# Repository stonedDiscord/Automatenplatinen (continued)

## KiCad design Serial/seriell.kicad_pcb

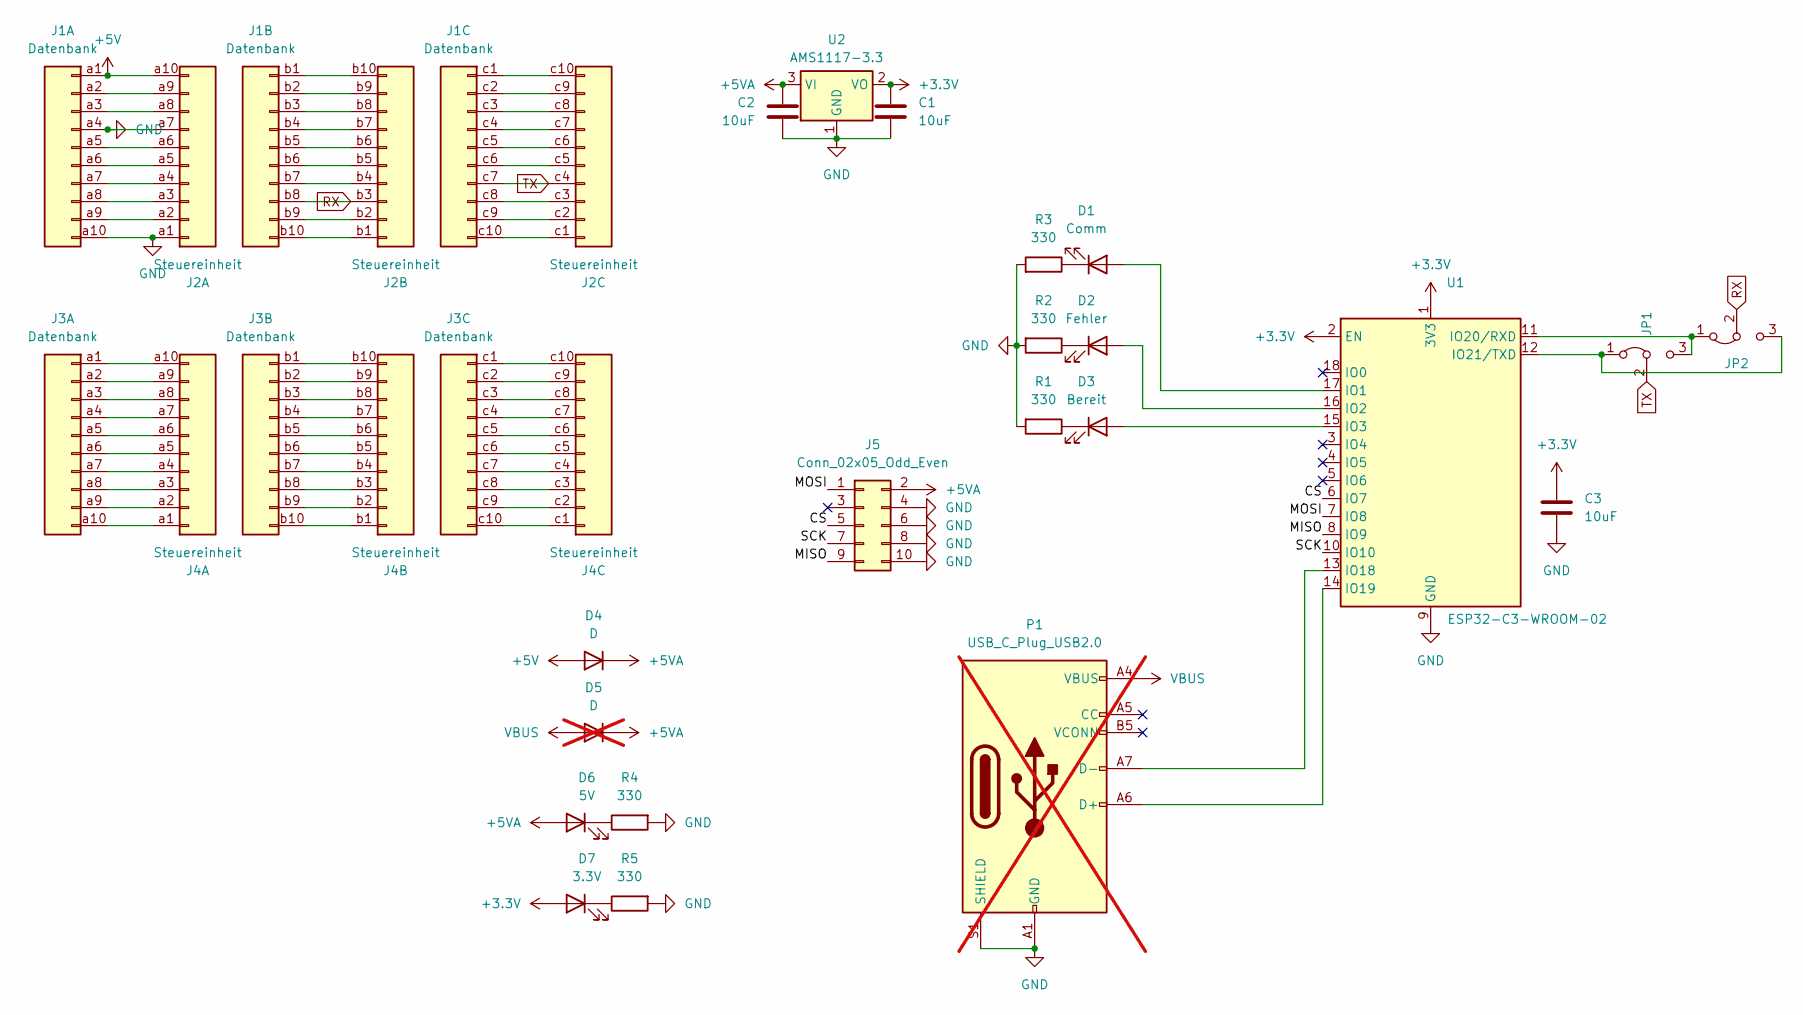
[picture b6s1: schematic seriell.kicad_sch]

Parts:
C1, C2, C3: 10uF; C_0603_1608Metric
D1: Comm; LED_0603_1608Metric
D2: Fehler; LED_0603_1608Metric
D3: Bereit; LED_0603_1608Metric
D4: D; D_SOD-123
D5: D; D_SOD-123; not fitted
D6: 5V; LED_0603_1608Metric
D7: 3.3V; LED_0603_1608Metric
J1, J3: Datenbank; DIN41612_C3_3x10_Female_Vertical_THT
J2, J4: Steuereinheit; DIN41612_R3_3x10_Male_Vertical_THT
J5: Conn_02x05_Odd_Even; IDC-Header_2x05_P2.54mm_Vertical
JP1: TX; SolderJumper-3_P1.3mm_Bridged2Bar12_Pad1.0x1.5mm
JP2: RX; SolderJumper-3_P1.3mm_Bridged2Bar12_Pad1.0x1.5mm
P1: USB_C_Plug_USB2.0; USB_C_Receptacle_G-Switch_GT-USB-7010ASV; not fitted
R1, R2, R3, R4, R5: 330; LED_0603_1608Metric
U1: ESP32-C3-WROOM-02
U2: AMS1117-3.3; SOT-223-3_TabPin2

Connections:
+3.3V: C1.1, C3.1, D7.2 (A), U1.1 (3V3), U1.2 (EN), U2.2 (VO)
+5V: D4.2 (A), J1.a1, J2.a10
+5VA: C2.1, D4.1 (K), D5.1 (K), D6.2 (A), J5.2, U2.3 (VI)
/CS: J5.5, U1.6 (IO7)
/MISO: J5.9, U1.8 (IO9)
/MOSI: J5.1, U1.7 (IO8)
/SCK: J5.7, U1.10 (IO10)
GND: C1.2, C2.2, C3.2, J1.a4, J1.a10, J2.a1, J2.a7, J5.4, J5.6, J5.8, J5.10, P1.A1 (GND), P1.A12 (GND), P1.B1 (GND), P1.B12 (GND), P1.S1 (SHIELD), R1.2, R2.2, R3.2, R4.2, R5.2, U1.9 (GND), U1.19 (GND), U2.1 (GND)
unnamed: D1.2 (A), U1.17 (IO1)
unnamed: D1.1 (K), R3.1
unnamed: D2.2 (A), U1.16 (IO2)
unnamed: D2.1 (K), R2.1
unnamed: D3.2 (A), U1.15 (IO3)
unnamed: D3.1 (K), R1.1
unnamed: D6.1 (K), R4.1
unnamed: D7.1 (K), R5.1
unnamed: J1.a2, J2.a9
unnamed: J1.a3, J2.a8
unnamed: J1.a5, J2.a6
unnamed: J1.a6, J2.a5
unnamed: J1.a7, J2.a4
unnamed: J1.a8, J2.a3
unnamed: J1.a9, J2.a2
unnamed: J1.b1, J2.b10
unnamed: J1.b2, J2.b9
unnamed: J1.b3, J2.b8
unnamed: J1.b4, J2.b7
unnamed: J1.b5, J2.b6
unnamed: J1.b6, J2.b5
unnamed: J1.b7, J2.b4
unnamed: J1.b9, J2.b2
unnamed: J1.b10, J2.b1
unnamed: J1.c1, J2.c10
unnamed: J1.c2, J2.c9
unnamed: J1.c3, J2.c8
unnamed: J1.c4, J2.c7
unnamed: J1.c5, J2.c6
unnamed: J1.c6, J2.c5
unnamed: J1.c8, J2.c3
unnamed: J1.c9, J2.c2
unnamed: J1.c10, J2.c1
unnamed: J3.a1, J4.a10
unnamed: J3.a2, J4.a9
unnamed: J3.a3, J4.a8
unnamed: J3.a4, J4.a7
unnamed: J3.a5, J4.a6
unnamed: J3.a6, J4.a5
unnamed: J3.a7, J4.a4
unnamed: J3.a8, J4.a3
unnamed: J3.a9, J4.a2
unnamed: J3.a10, J4.a1
unnamed: J3.b1, J4.b10
unnamed: J3.b2, J4.b9
unnamed: J3.b3, J4.b8
unnamed: J3.b4, J4.b7
unnamed: J3.b5, J4.b6
unnamed: J3.b6, J4.b5
unnamed: J3.b7, J4.b4
unnamed: J3.b8, J4.b3
unnamed: J3.b9, J4.b2
unnamed: J3.b10, J4.b1
unnamed: J3.c1, J4.c10
unnamed: J3.c2, J4.c9
unnamed: J3.c3, J4.c8
unnamed: J3.c4, J4.c7
unnamed: J3.c5, J4.c6
unnamed: J3.c6, J4.c5
unnamed: J3.c7, J4.c4
unnamed: J3.c8, J4.c3
unnamed: J3.c9, J4.c2
unnamed: J3.c10, J4.c1
unnamed: JP1.1 (A), JP2.3 (B), U1.12 (IO21/TXD)
unnamed: JP1.3 (B), JP2.1 (A), U1.11 (IO20/RXD)
unnamed: P1.A6 (D+), U1.14 (IO19)
unnamed: P1.A7 (D-), U1.13 (IO18)
RX: J1.b8, J2.b3, JP2.2 (C)
TX: J1.c7, J2.c4, JP1.2 (C)
VBUS: D5.2 (A), P1.A4 (VBUS), P1.A9 (VBUS), P1.B4 (VBUS), P1.B9 (VBUS)

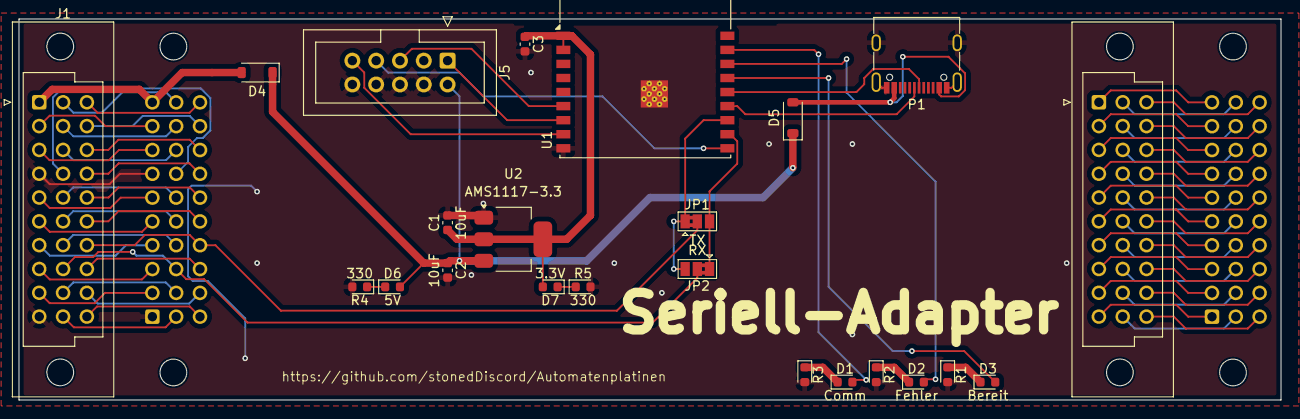
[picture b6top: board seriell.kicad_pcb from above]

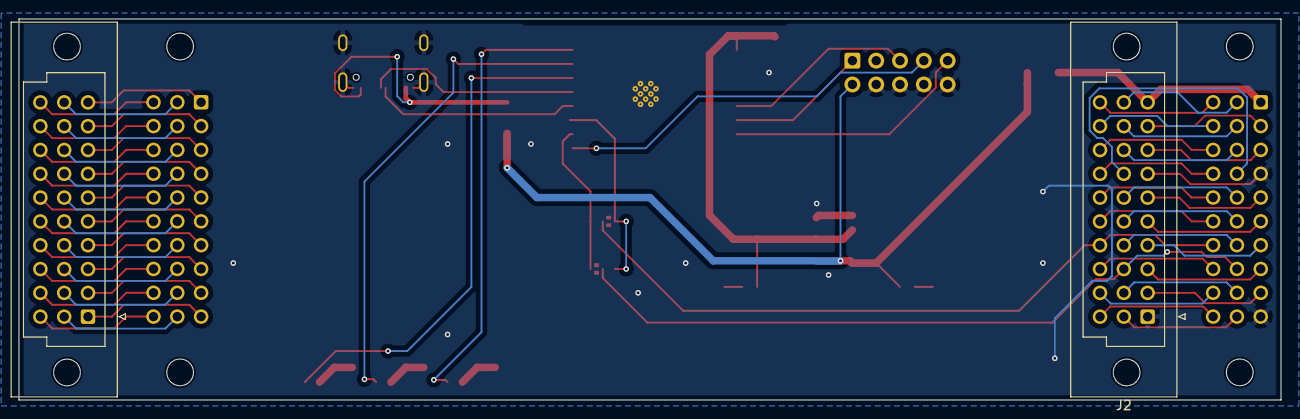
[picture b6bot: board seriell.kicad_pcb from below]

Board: 2 copper layers, 134.6 x 40.6 mm, 25 parts (2 on the bottom side), 78 nets.

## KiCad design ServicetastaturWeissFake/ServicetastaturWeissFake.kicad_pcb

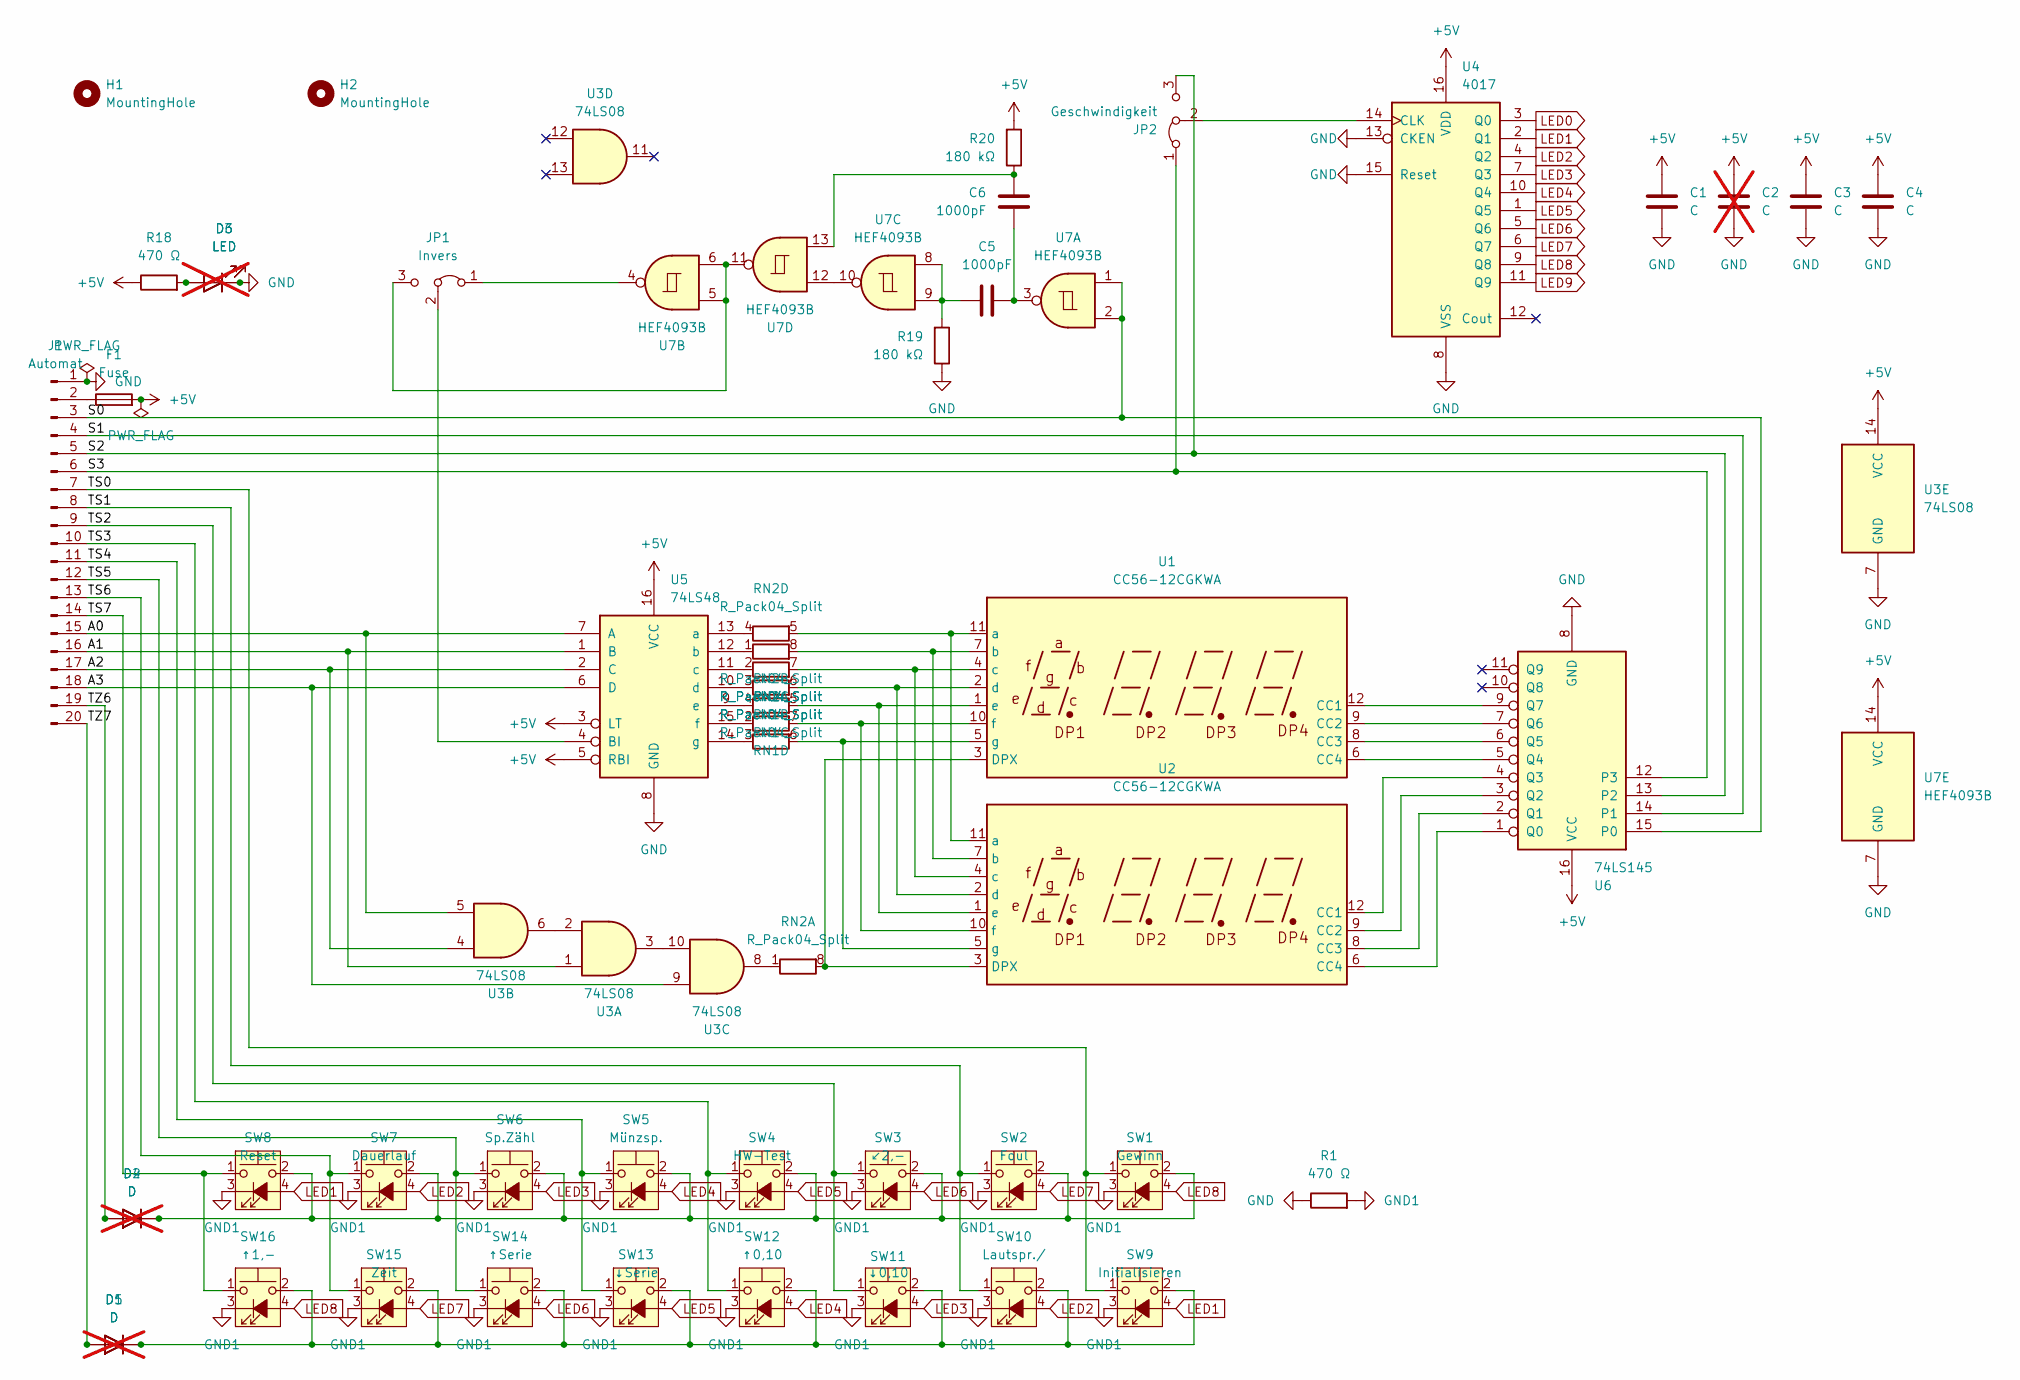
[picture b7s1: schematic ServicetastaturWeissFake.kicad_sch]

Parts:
C1: C; C_Disc_D4.3mm_W1.9mm_P5.00mm
C2: C; C_Disc_D4.3mm_W1.9mm_P5.00mm; not fitted
C3, C4: C; C_0603_1608Metric
C5, C6: 1000pF; C_0603_1608Metric
D1, D2: D; D_A-405_P10.16mm_Horizontal; not fitted
D3: LED; LED_D3.0mm; not fitted
D4, D5: D; D_SOD-128
D6: LED; LED_0805_2012Metric
F1: Fuse; Fuse_0805_2012Metric
H1, H2: MountingHole; MountingHole_3.2mm_M3
J1: Automat; PinHeader_1x20_P2.54mm_Vertical
JP1: Invers; SolderJumper-3_P1.3mm_Bridged12_Pad1.0x1.5mm
JP2: Geschwindigkeit; SolderJumper-3_P1.3mm_Bridged12_Pad1.0x1.5mm
R1, R18: 470 Ω; R_0603_1608Metric
R19, R20: 180 kΩ; R_0603_1608Metric
RN1, RN2: R_Pack04_Split; R_Array_Convex_4x0603
SW1: Gewinn; SW_SPST_Combination_12mm
SW2: Foul; SW_SPST_Combination_12mm
SW3: ↙2,-; SW_SPST_Combination_12mm
SW4: HW-Test; SW_SPST_Combination_12mm
SW5: Münzsp.; SW_SPST_Combination_12mm
SW6: Sp.Zähl; SW_SPST_Combination_12mm
SW7: Dauerlauf; SW_SPST_Combination_12mm
SW8: Reset; SW_SPST_Combination_12mm
SW9: Initialisieren; SW_SPST_Combination_12mm
SW10: Lautspr./; SW_SPST_Combination_12mm
SW11: ↓0,10; SW_SPST_Combination_12mm
SW12: ↑0,10; SW_SPST_Combination_12mm
SW13: ↓Serie; SW_SPST_Combination_12mm
SW14: ↑Serie; SW_SPST_Combination_12mm
SW15: Zeit; SW_SPST_Combination_12mm
SW16: ↑1,-; SW_SPST_Combination_12mm
U1, U2: CC56-12CGKWA; CA56-12CGKWA
U3: 74LS08; SOIC-14_3.9x8.7mm_P1.27mm
U4: 4017; SOIC-16_3.9x9.9mm_P1.27mm
U5: 74LS48; SOIC-16_4.55x10.3mm_P1.27mm
U6: 74LS145; SOIC-16_4.55x10.3mm_P1.27mm
U7: HEF4093B; SOIC-14_3.9x8.7mm_P1.27mm

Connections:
+5V: C1.1, C2.1, C3.1, C4.1, F1.2, R18.1, R20.2, U3.14 (VCC), U4.16 (VDD), U5.3 (LT), U5.5 (RBI), U5.16 (VCC), U6.16 (VCC), U7.14 (VCC)
/A0: J1.15, U3.5, U5.7 (A)
/A1: J1.16, U3.1, U5.1 (B)
/A2: J1.17, U3.4, U5.2 (C)
/A3: J1.18, U3.9, U5.6 (D)
/S0: J1.3, U6.15 (P0), U7.1, U7.2
/S1: J1.4, U6.14 (P1)
/S2: J1.5, JP2.3 (B), U6.13 (P2)
/S3: J1.6, JP2.1 (A), U6.12 (P3)
/TS0: J1.7, SW1.1, SW9.1
/TS1: J1.8, SW2.1, SW10.1
/TS2: J1.9, SW3.1, SW11.1
/TS3: J1.10, SW4.1, SW12.1
/TS4: J1.11, SW5.1, SW13.1
/TS5: J1.12, SW6.1, SW14.1
/TS6: J1.13, SW7.1, SW15.1
/TS7: J1.14, SW8.1, SW16.1
/TZ6: D2.2 (A), D4.2 (A), J1.19
/TZ7: D1.2 (A), D5.2 (A), J1.20
GND: C1.2, C2.2, C3.2, C4.2, D3.1 (K), D6.1 (K), J1.1, R1.1, R19.1, U3.7 (GND), U4.8 (VSS), U4.13 (CKEN), U4.15 (Reset), U5.8 (GND), U6.8 (GND), U7.7 (GND)
GND1: R1.2, SW1.3 (K), SW2.3 (K), SW3.3 (K), SW4.3 (K), SW5.3 (K), SW6.3 (K), SW7.3 (K), SW8.3 (K), SW9.3 (K), SW10.3 (K), SW11.3 (K), SW12.3 (K), SW13.3 (K), SW14.3 (K), SW15.3 (K), SW16.3 (K)
LED0: U4.3 (Q0)
LED1: SW8.4 (A), SW9.4 (A), U4.2 (Q1)
LED2: SW7.4 (A), SW10.4 (A), U4.4 (Q2)
LED3: SW6.4 (A), SW11.4 (A), U4.7 (Q3)
LED4: SW5.4 (A), SW12.4 (A), U4.10 (Q4)
LED5: SW4.4 (A), SW13.4 (A), U4.1 (Q5)
LED6: SW3.4 (A), SW14.4 (A), U4.5 (Q6)
LED7: SW2.4 (A), SW15.4 (A), U4.6 (Q7)
LED8: SW1.4 (A), SW16.4 (A), U4.9 (Q8)
LED9: U4.11 (Q9)
unnamed: C5.1, C6.1, U7.3
unnamed: C5.2, R19.2, U7.8, U7.9
unnamed: C6.2, R20.1, U7.13
unnamed: D1.1 (K), D5.1 (K), SW9.2, SW10.2, SW11.2, SW12.2, SW13.2, SW14.2, SW15.2, SW16.2
unnamed: D2.1 (K), D4.1 (K), SW1.2, SW2.2, SW3.2, SW4.2, SW5.2, SW6.2, SW7.2, SW8.2
unnamed: D3.2 (A), D6.2 (A), R18.2
unnamed: F1.1, J1.2
unnamed: JP1.1 (A), U7.4
unnamed: JP1.3 (B), U7.5, U7.6, U7.11
unnamed: JP1.2 (C), U5.4 (BI)
unnamed: JP2.2 (C), U4.14 (CLK)
unnamed: RN1.1 (R1.1), U5.12 (b)
unnamed: RN1.8 (R1.2), U1.7 (b), U2.7 (b)
unnamed: RN1.2 (R2.1), U5.11 (c)
unnamed: RN1.7 (R2.2), U1.4 (c), U2.4 (c)
unnamed: RN1.3 (R3.1), U5.10 (d)
unnamed: RN1.6 (R3.2), U1.2 (d), U2.2 (d)
unnamed: RN1.4 (R4.1), U5.9 (e)
unnamed: RN1.5 (R4.2), U1.1 (e), U2.1 (e)
unnamed: RN2.1 (R1.1), U3.8
unnamed: RN2.8 (R1.2), U1.3 (DPX), U2.3 (DPX)
unnamed: RN2.2 (R2.1), U5.15 (f)
unnamed: RN2.7 (R2.2), U1.10 (f), U2.10 (f)
unnamed: RN2.3 (R3.1), U5.14 (g)
unnamed: RN2.6 (R3.2), U1.5 (g), U2.5 (g)
unnamed: RN2.4 (R4.1), U5.13 (a)
unnamed: RN2.5 (R4.2), U1.11 (a), U2.11 (a)
unnamed: U1.12 (CC1), U6.9 (Q7)
unnamed: U1.9 (CC2), U6.7 (Q6)
unnamed: U1.8 (CC3), U6.6 (Q5)
unnamed: U1.6 (CC4), U6.5 (Q4)
unnamed: U2.12 (CC1), U6.4 (Q3)
unnamed: U2.9 (CC2), U6.3 (Q2)
unnamed: U2.8 (CC3), U6.2 (Q1)
unnamed: U2.6 (CC4), U6.1 (Q0)
unnamed: U3.2, U3.6
unnamed: U3.3, U3.10
unnamed: U7.10, U7.12

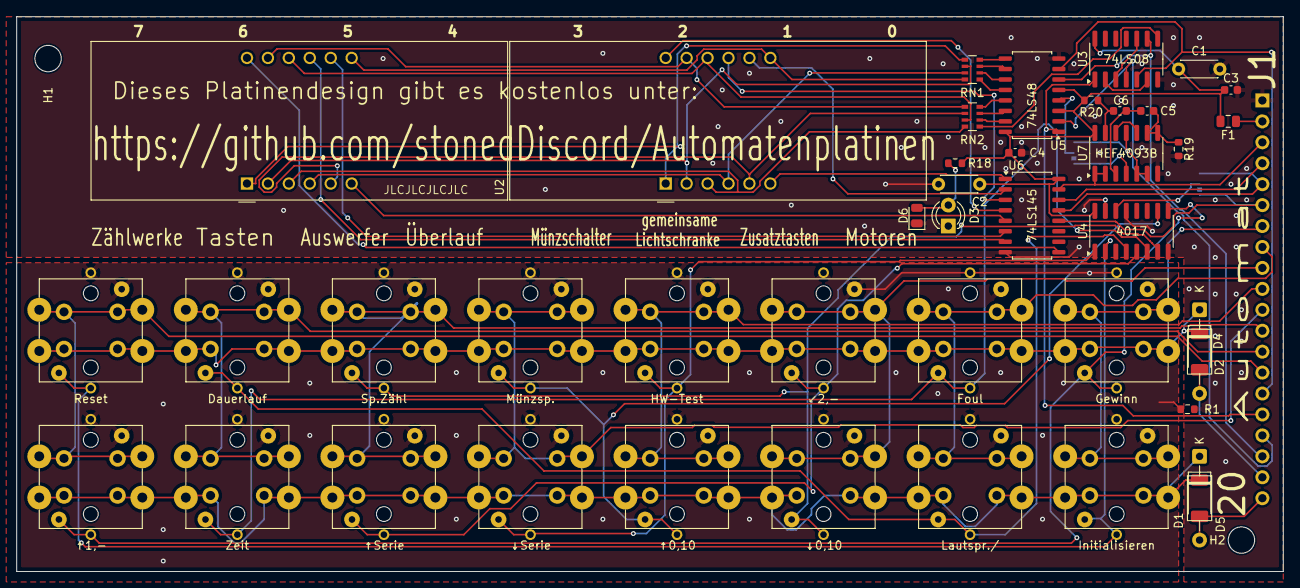
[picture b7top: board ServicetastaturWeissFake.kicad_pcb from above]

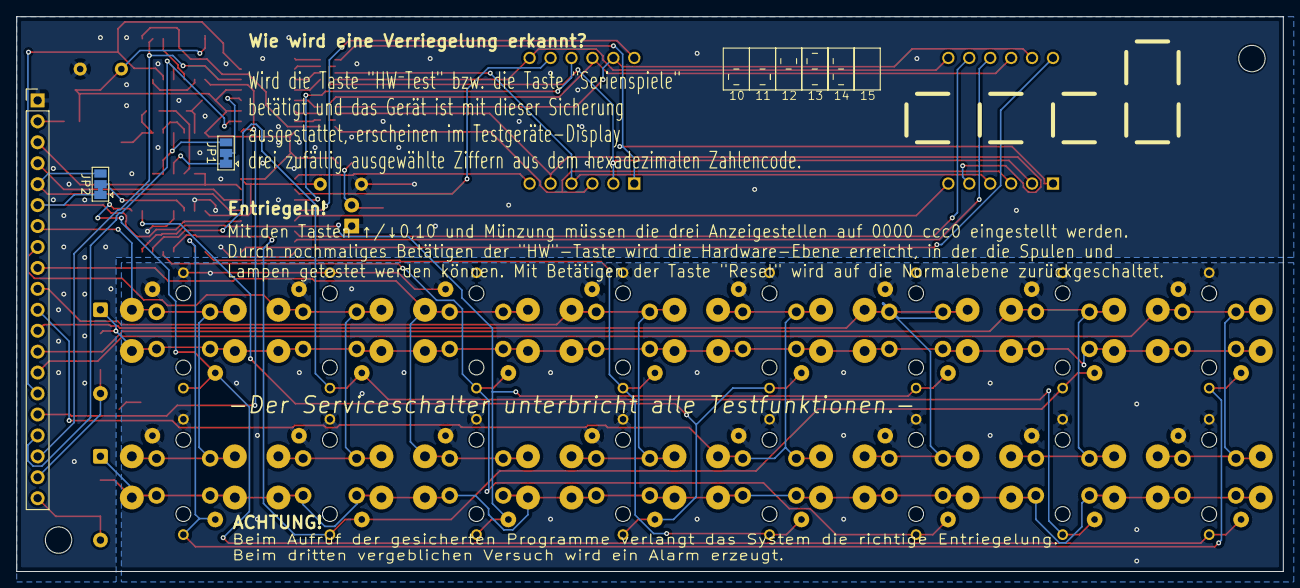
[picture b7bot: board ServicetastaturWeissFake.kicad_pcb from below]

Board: 2 copper layers, 153.7 x 67.3 mm, 47 parts (3 on the bottom side), 67 nets.
